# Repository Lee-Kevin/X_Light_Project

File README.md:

# RGBLED_Ligh Controller Hardware Part
For this project, the hardware part is very import, We buy a RGB bulb from Huaqiang North in ShenZhen, it's something just like below picture shows.

The factory version of the bulb is controlled by an IR Remote controller, for this project, we want to control the bulbs by group or control each bulb independently. So we did a special pcb for this bulb. Just like below picture shows.

I remove the IR reciver from the factory version, and connect the original IR Reciver Pin to the new board, After assembling the bulb is just as shown in the following figure.

About the pcb and the schematic file, you can click **[here](https://github.com/Lee-Kevin/X_Light_Project/tree/master/Hardware)** to download.

# RGBLED_Ligh Controller Software Part
------
In this project, the software has two part, one is the slave part and the another one is master part.

The slave part will connect to a RGB light, and control the color of the light, the communication between slave and master is wireless/RF.

## Slave Part

This part will recive the command from the master part.

The data frame is:

Head  -  Address  -  Command  -  End

0xAA  -    Addr   -  Command  -  0x55

The Address is a uint8_t value range from 0~255, and 255 is the boardcast address, and 0 is a reserved address.

The Command is something like this:
``` C 
enum LEDstatus {
    led_on            = 0,
    led_off           = 1,
    led_down          = 2,
    led_up            = 3,
    led_red           = 4,
    led_green         = 5,
    led_blue          = 6,
    led_white         = 7,
    led_lightSalmon   = 8,
    led_orangeRed     = 9,
    led_orange        = 10,
    led_yellow        = 11,
    led_paleGreen     = 12,
    led_skyBlue       = 13,
    led_turquoise     = 14,
    led_royalBlue     = 15,
    led_steelBlue     = 16,
    led_purple        = 17,
    led_rebeccapurple = 18,
    led_orchid        = 19,
    led_flash         = 20,
    led_strobe        = 21,
    led_fade          = 22,
    led_smooth        = 23,
    
};
typedef enum LEDstatus ledstatus_t;
ledstatus_t eLEDStatus;
```

The slave part can also set the address via UART, and the command data is like this:

Head  --  Addr  --  Command  -- New Addr  --  END

0xAA  --  0xFF  --   0xFF    --  New Addr --  0x55

Then you can also get the slave address by send the following command:

Head  --  Addr  --  Command  --  END

0xAA  --  0xFF  --   0xFE    --  0x55

Note: the 0xFF is the boardcast addr.

## Master Part

For this system, there can be many master parts to control the light, the only thing that master part need to do is sending commands.

The Master part1 is used for sending command to the slave part, and this part has the following functions.
1. Recive IR command from the IR controller.
2. Recive comand from the computer(just recive data from uart,and send it out via software serial).
3. Change the display mode by a button.
4. Turn ON/OFF the light by a button

More master part to be continued.

## The Light Number 

The following picture shows how the Light is arrranged.

## The finished work

to be continued

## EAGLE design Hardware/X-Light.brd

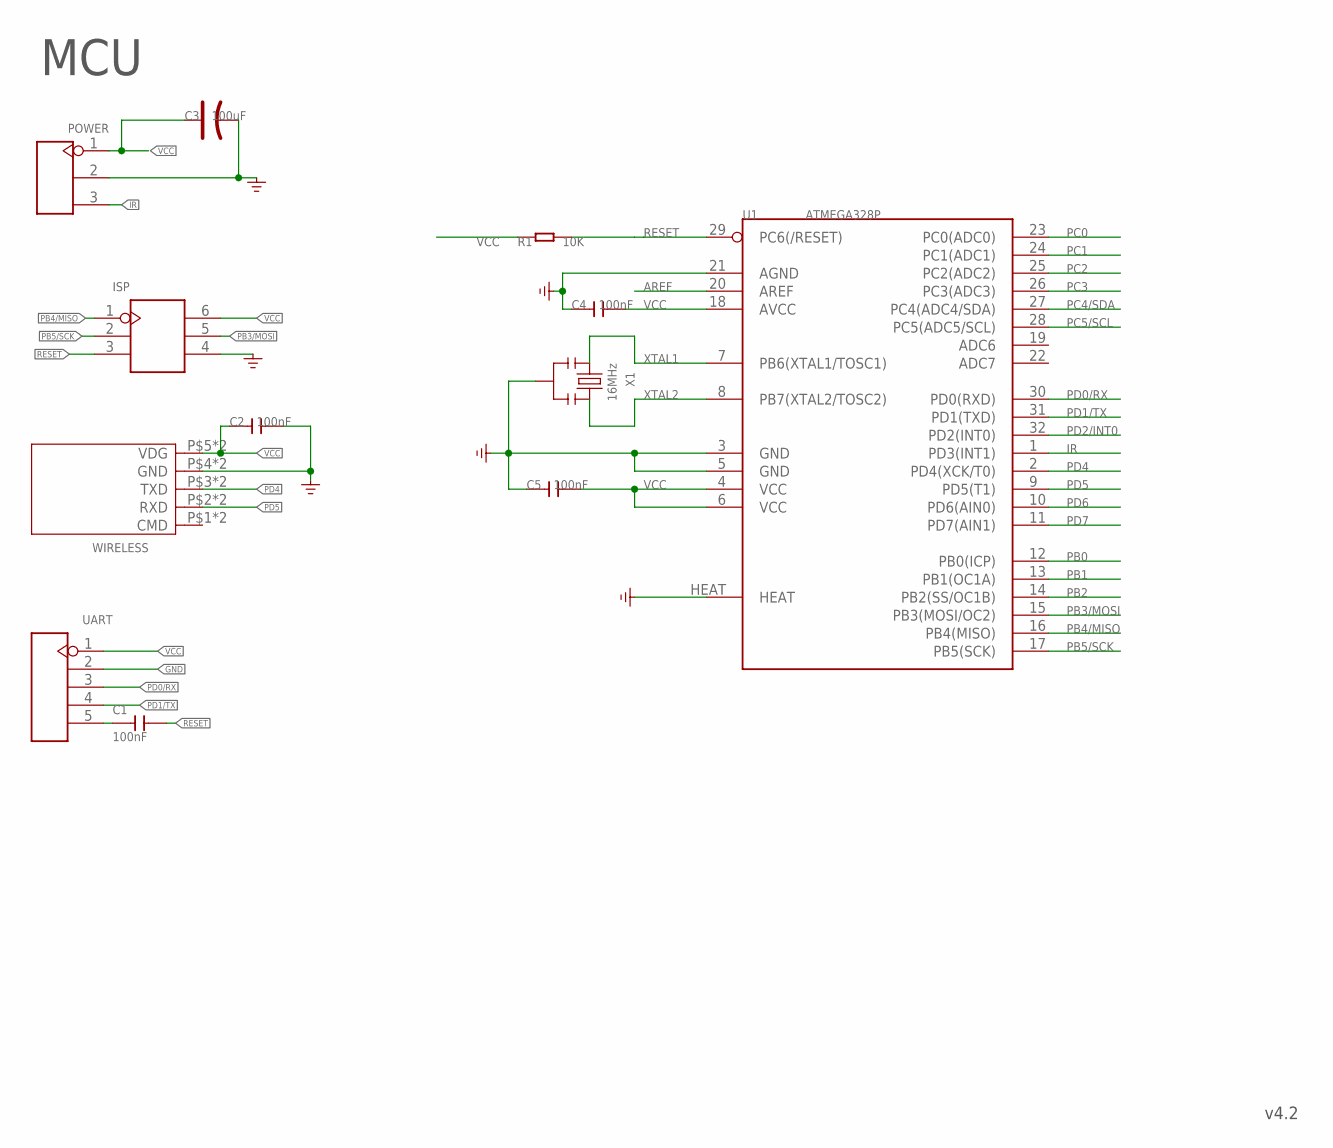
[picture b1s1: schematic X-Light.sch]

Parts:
C1, C2, C4, C5: 100nF; C0603
C3: 100uF; AVX-C
ISP: HEADER-2X3P-2.54; H2X3-2.54
POWER: HEADER-3P-2.54; H3-2.54
R1: 10K; R0603
U1: ATMEGA328P; MLF32X
UART: HEADER-5P-2.54; H5-2.54
WIRELESS: MOUDLE-5P; 5P-24.2X12.4MM-2.54
X1: 16MHz; 3P-SMD-3.6X1.3

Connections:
AREF: U1.20 (AREF)
GND: C2.2, C3.-, C4.1, C5.1, ISP.4, POWER.2, U1.3 (GND), U1.5 (GND), U1.21 (AGND), U1.HEAT, UART.2, WIRELESS.P4 (GND), WIRELESS.P$4 (GND), X1.2
IR: POWER.3, U1.1 (PD3(INT1))
unnamed: C1.1, UART.5
PB0: U1.12 (PB0(ICP))
PB1: U1.13 (PB1(OC1A))
PB2: U1.14 (PB2(SS/OC1B))
PB3/MOSI: ISP.5, U1.15 (PB3(MOSI/OC2))
PB4/MISO: ISP.1, U1.16 (PB4(MISO))
PB5/SCK: ISP.2, U1.17 (PB5(SCK))
PC0: U1.23 (PC0(ADC0))
PC1: U1.24 (PC1(ADC1))
PC2: U1.25 (PC2(ADC2))
PC3: U1.26 (PC3(ADC3))
PC4/SDA: U1.27 (PC4(ADC4/SDA))
PC5/SCL: U1.28 (PC5(ADC5/SCL))
PD0/RX: U1.30 (PD0(RXD)), UART.3
PD1/TX: U1.31 (PD1(TXD)), UART.4
PD2/INT0: U1.32 (PD2(INT0))
PD4: U1.2 (PD4(XCK/T0)), WIRELESS.P3 (TXD), WIRELESS.P$3 (TXD)
PD5: U1.9 (PD5(T1)), WIRELESS.P2 (RXD), WIRELESS.P$2 (RXD)
PD6: U1.10 (PD6(AIN0))
PD7: U1.11 (PD7(AIN1))
RESET: C1.2, ISP.3, R1.2, U1.29 (PC6(/RESET))
VCC: C2.1, C3.+, C4.2, C5.2, ISP.6, POWER.1, R1.1, U1.4 (VCC), U1.6 (VCC), U1.18 (AVCC), UART.1, WIRELESS.P5 (VDG), WIRELESS.P$5 (VDG)
XTAL1: U1.7 (PB6(XTAL1/TOSC1)), X1.1
XTAL2: U1.8 (PB7(XTAL2/TOSC2)), X1.3

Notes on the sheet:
MCU
v4.2

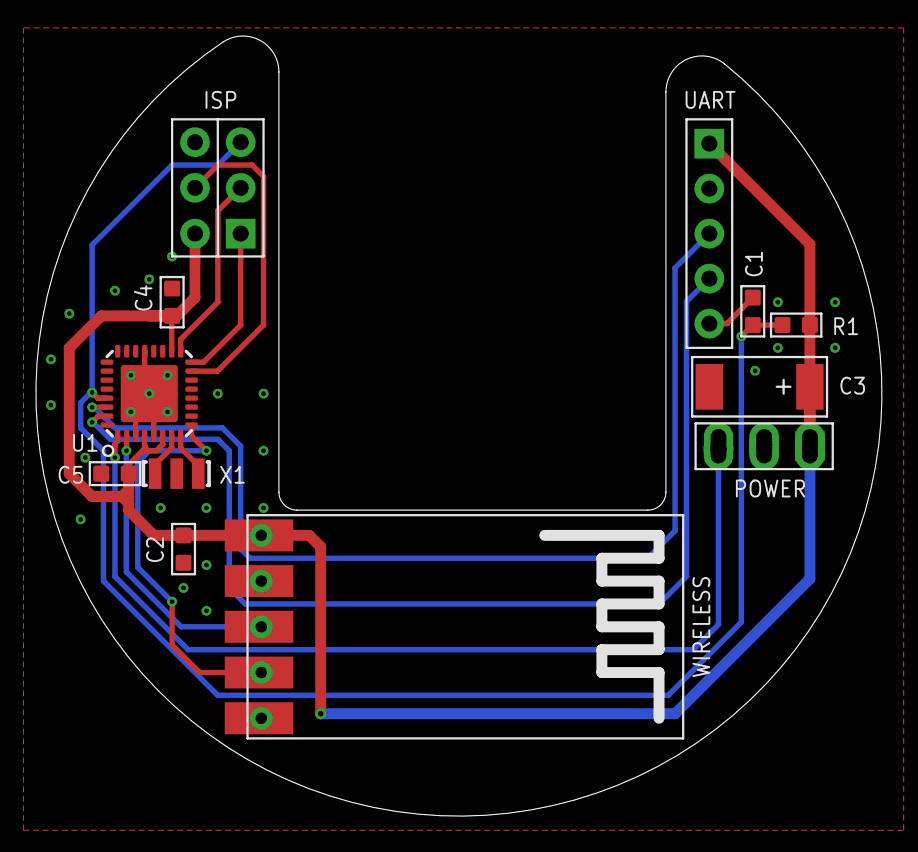
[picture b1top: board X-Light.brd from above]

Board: 2 copper layers, 47.0 x 43.3 mm, 12 parts (0 on the bottom side), 14 nets.

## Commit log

2017-03-13 Finish the project
2017-04-17 update the document and add the eagle file
2017-04-17 update the document and add picturr
